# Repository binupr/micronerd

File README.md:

# micronerd
More information to be added

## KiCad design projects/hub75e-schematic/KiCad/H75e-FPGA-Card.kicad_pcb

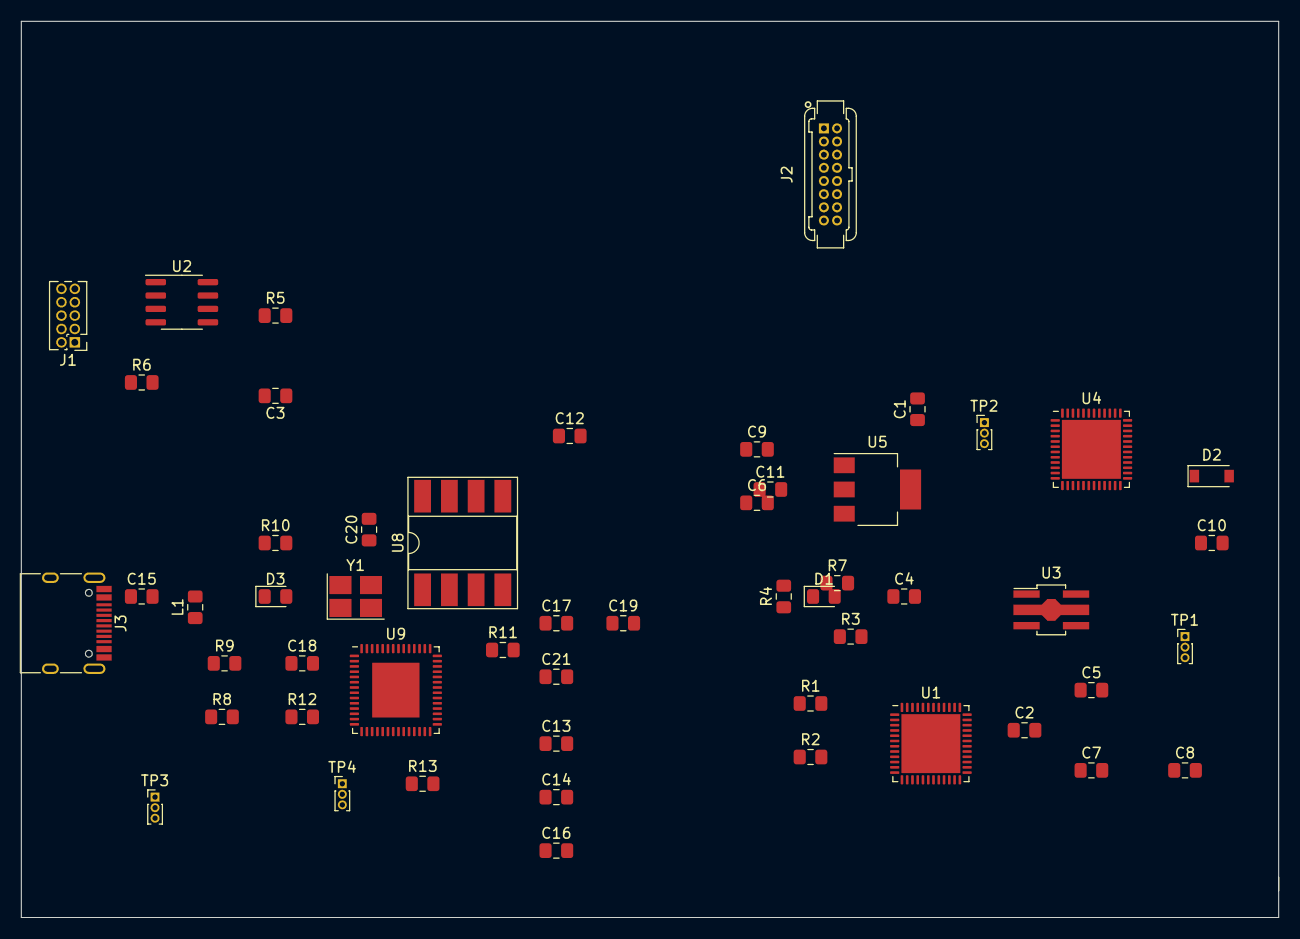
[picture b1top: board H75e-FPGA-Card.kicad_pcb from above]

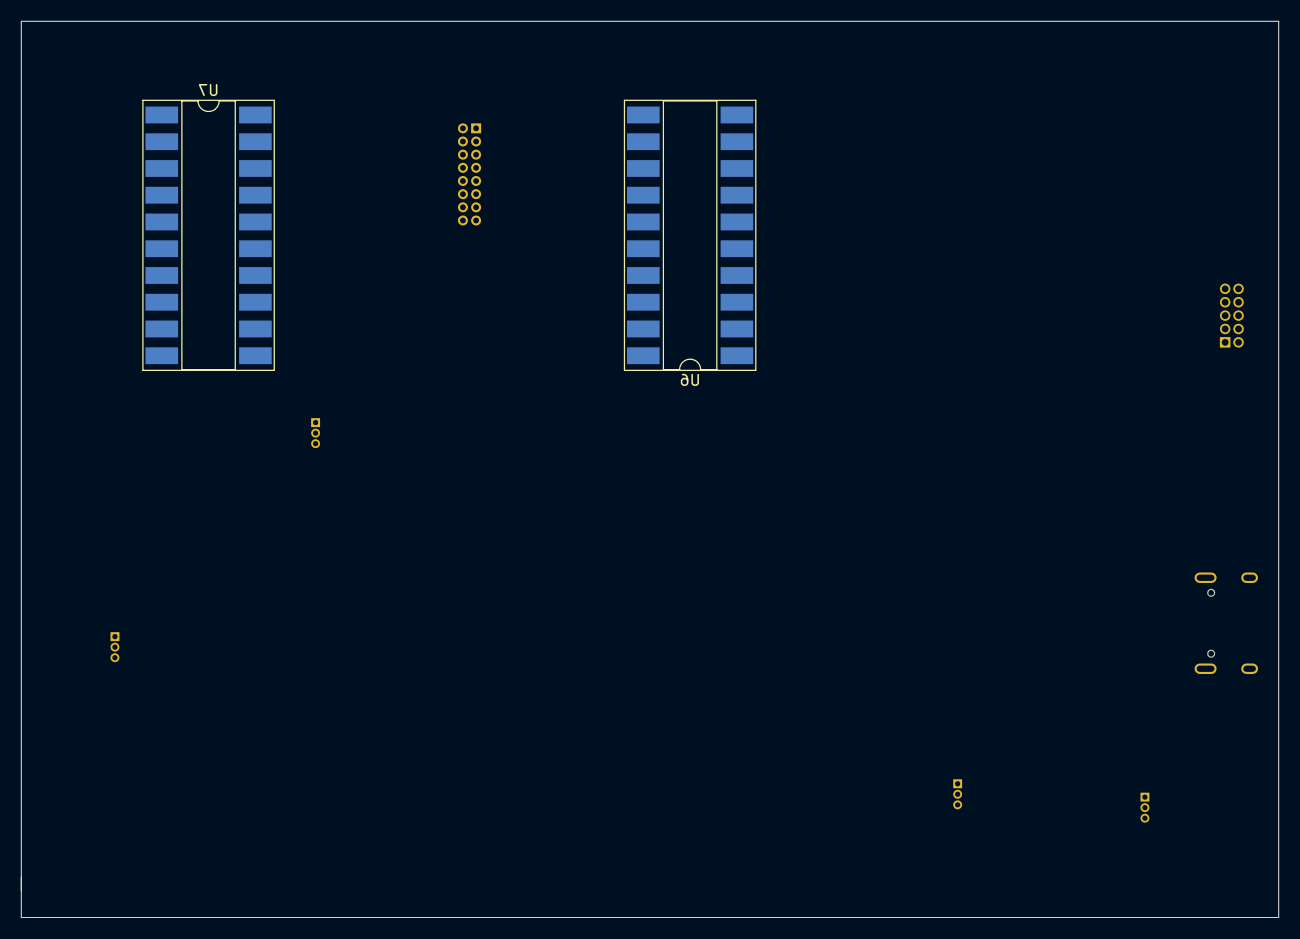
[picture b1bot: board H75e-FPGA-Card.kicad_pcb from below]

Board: 2 copper layers, 119.4 x 85.1 mm, 55 parts (2 on the bottom side), 75 nets, no tracks yet.

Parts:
C1, C2, C3, C4, C5, C6, C8, C9, C10, C11, C12, C13, C14, C17, C21: 100n; C_0805_2012Metric_Pad1.15x1.40mm_HandSolder
C7, C16, C19: 1u; C_0805_2012Metric_Pad1.15x1.40mm_HandSolder
C15, C18, C20: 18p; C_0805_2012Metric_Pad1.15x1.40mm_HandSolder
D1, D3: LED; LED_0805_2012Metric_Pad1.15x1.40mm_HandSolder
D2: MBR0520; D_SOD-123
J1: Conn_ARM_JTAG_SWD_10; PinHeader_2x05_P1.27mm_Vertical
J2: Conn_02x08_Odd_Even; Harwin_Gecko-G125-MVX1605L1X_2x08_P1.25mm_Vertical
J3: USB_C_Recept_16Pin; USB_C_Receptacle_HRO_TYPE-C-31-M-12
L1: 22R; L_0805_2012Metric_Pad1.15x1.40mm_HandSolder
R1: 10K; R_0805_2012Metric_Pad1.15x1.40mm_HandSolder
R2, R11: 2.2K; R_0805_2012Metric_Pad1.15x1.40mm_HandSolder
R3, R4, R5, R6, R7: R; R_0805_2012Metric_Pad1.15x1.40mm_HandSolder
R8, R9, R10: 5.1K; R_0805_2012Metric_Pad1.15x1.40mm_HandSolder
R12, R13: 12K; R_0805_2012Metric_Pad1.15x1.40mm_HandSolder
TP1, TP2, TP3, TP4: TestPoint; PinHeader_1x03_P1.00mm_Vertical
U1, U4: ICE40UP5K-SG48ITR; QFN-48-1EP_7x7mm_P0.5mm_EP5.6x5.6mm
U2: AT25SF081-SSHD-X; SOIC-8_3.9x4.9mm_P1.27mm
U3: AZ1117-1.2; SOT-89-5_Handsoldering
U5: AP1117-33; SOT-223-3_TabPin2
U6, U7: 74HC245; DIP-20_W8.89mm_SMDSocket_LongPads
U8: 93LCxxB; DIP-8_W8.89mm_SMDSocket_LongPads
U9: FT232H; QFN-56-1EP_8x8mm_P0.5mm_EP4.5x5.2mm
Y1: 12Mhz; Crystal_SMD_SeikoEpson_TSX3225-4Pin_3.2x2.5mm_HandSoldering

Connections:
+1V2: C5.1, C7.1, C8.1, TP1.1, U3.2, U4.5, U4.29, U4.30
+1V8: C17.1, C19.1, U9.38
+3.3VA: C13.1, C14.1, C16.1, R13.1, TP4.1, U8.8, U9.3, U9.8, U9.12, U9.24, U9.34, U9.39, U9.46
+3V3: C1.1, C2.1, C3.1, C4.1, C9.1, C10.1, D2.2, J1.1, R1.1, R2.1, R3.1, R4.1, R5.1, R6.1, R7.1, TP2.1, U1.1, U1.22, U1.33, U2.8, U3.3, U5.2
+5V: C6.1, C11.1, C12.1, C15.1, D3.2, L1.1, U5.3, U6.1, U6.20, U7.1, U7.20, U9.40
A0: U1.28, U6.5
A1: U1.37, U7.6
A2: U1.31, U6.4
A3: U1.36, U7.7
A4: U1.38, U7.5
B0: U1.25, U6.8
B1: U1.27, U6.6
BLANK: U1.34, U6.2
CS: J1.2, R4.2, U1.16, U2.1
D0: U1.21, U9.13
D1: U1.20, U9.14
D2: U1.13, U9.15
D3: U1.12, U9.16
D4: U1.11, U9.17
D5: U1.10, U9.18
D6: U1.9, U9.19
D7: U1.6, U9.20
D8: U1.4, U9.21
D9: U1.3, U9.25
D10: U1.2, U9.26
D11: U1.48, U9.27
D12: U1.47, U9.28
D13: U1.46, U9.29
D14: U1.45, U9.30
D15: U1.44, U9.31
G0: U1.43, U7.2
G1: U1.42, U7.4
GND: C1.2, C2.2, C3.2, C4.2, C5.2, C6.2, C7.2, C8.2, C9.2, C10.2, C11.2, C12.2, C13.2, C14.2, C15.2, C16.2, C17.2, C18.2, C19.2, C20.2, C21.2, D1.1, J1.3, J1.5, J1.9, J2.4, J2.16, J3.A1, J3.A12, J3.B1, J3.B12, J3.S1, R8.1, R9.1, R10.1, R12.2, TP3.1, U2.4, U3.1, U4.49, U5.1, U8.5, U9.4, U9.9, U9.10, U9.11, U9.22, U9.23, U9.35, U9.36, U9.41, U9.42, U9.47, U9.48, Y1.2, Y1.4
LATCH: U1.35, U7.8
unnamed: C18.1, U9.1, Y1.1
unnamed: C20.1, U9.2, Y1.3
unnamed: C21.1, U9.37
unnamed: D1.2, R2.2, U1.7
unnamed: D2.1, U4.24
unnamed: D3.1, R10.2
unnamed: J2.1, U6.11
unnamed: J2.2, U7.18
unnamed: J2.3, U6.12
unnamed: J2.5, U6.13
unnamed: J2.6, U7.16
unnamed: J2.7, U6.14
unnamed: J2.8, U7.15
unnamed: J2.9, U6.15
unnamed: J2.10, U7.14
unnamed: J2.11, U6.16
unnamed: J2.12, U7.13
unnamed: J2.13, U6.17
unnamed: J2.14, U7.12
unnamed: J2.15, U6.18
unnamed: J3.A4, J3.A9, J3.B4, J3.B9, L1.2
unnamed: J3.A5, R9.2
unnamed: J3.A6, J3.B6, U9.7
unnamed: J3.A7, J3.B7, U9.6
unnamed: J3.B5, R8.2
unnamed: R6.2, U2.3
unnamed: R7.2, U2.7
unnamed: R11.1, U8.3, U9.43
unnamed: R11.2, U8.4
unnamed: R12.1, U9.5
unnamed: U6.10, U6.19
unnamed: U7.10, U7.19
unnamed: U8.1, U9.45
unnamed: U8.2, U9.44
R0: U1.23, U6.9
R1: U1.26, U6.7
RST: J1.10, R1.2, U1.8
SCK: J1.4, R5.2, U1.15, U2.6
SCLK: U1.32, U6.3
SDI: J1.6, U1.17, U2.2
SDO: J1.8, R3.2, U1.14, U2.5

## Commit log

2020-09-05 My first commit of files from Home projects
2021-01-24 Create Readme
    README file for the Kicad folder
2021-01-24 Create Makefile
2021-07-11 Cleaning up workspace
2021-07-11 Minor code mod
2021-07-11 Testing git cli
